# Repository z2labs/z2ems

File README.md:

# Z2 EMS

Electromagnetic simulation of printed circuit boards, straight from KiCad.

Z2 EMS is a distribution of [openEMS](https://openEMS.de) (the free FDTD field solver by Thorsten Liebig and
contributors) with the parts a PCB designer needs on top:

- **KiCad importer** (`CSXCAD.KiCadImport`): copper of every layer, plated holes, board outline and stackup are
  read straight from a `.kicad_pcb` file; two-pad R/L/C footprints become lumped elements. Fab stackup presets
  (`CSXCAD.FabStackups`, e.g. JLCPCB JLC04161H-7628) and laminate dispersion / copper roughness models
  (`CSXCAD.PCBMaterials`).
- **Board to S-parameters in one command** (`twin/kicad_sim.py`): lumped ports at the connector pads, an
  automatic mesh for PCB geometry (thirds rule on strip edges, diagonal tracks, via antipads, graded cells),
  one run per port, Touchstone output, Z0 and effective permittivity of a line, a mesh DRC that finds copper
  shorted or broken by the staircase mesh before a run.
- **CUDA engine** (`--engine=cuda`): the FDTD update, the absorbing boundaries, excitation, lumped RLC and
  dispersive materials on an NVIDIA GPU, with a memory guard that catches corrupted GPU memory instead of
  returning a wrong result.
- **Conformal PEC** (contour-path FDTD after Yu and Mittra, 2001): a Yee edge partly covered by metal
  keeps the free fraction of its length, so metal edges that do not fall on a mesh line are not snapped
  to it. On the 50 Ω test coupon this moves Z0 from 50.37 Ω (staircase) to 49.50 Ω, against 49.35 Ω
  from the closed-form formula. On by default in the twin, `Z2_CONFORMAL=0` turns it off.
- **Viewer and local server** (`gui/`): a browser 3D view of the board (exploded layers, components) that
  can also start runs and show S-parameters, field maps and far field.
- **KiCad plugin**: [z2labs/z2ems-kicad](https://github.com/z2labs/z2ems-kicad) drives all of the above from
  the PCB editor (ports, stackup, mesh preview, simulate, field overlays).

## Repository layout

```
openEMS/        submodule: z2labs/z2ems-openEMS  (openEMS + CUDA engine, conformal PEC)
CSXCAD/         submodule: z2labs/z2ems-CSXCAD   (CSXCAD + KiCad importer, fab stackups, PCB materials)
fparser, QCSXCAD, AppCSXCAD, CTB   submodules: upstream (thliebig)
twin/           KiCad board -> openEMS model -> S-parameters (see twin/README.md)
gui/            3D viewer and local simulation server (see gui/README.md)
examples/       test coupons and a worked antenna example (see examples/README.md)
scripts/        dependency installer, Python build, Windows bundling
doc-src/        openEMS documentation sources
```

## Install

**Windows:** download the engine package from the
[releases](https://github.com/z2labs/z2ems/releases) and unzip it, e.g. to `%LOCALAPPDATA%\Z2EMS\engine` (where
the KiCad plugin looks first). It contains the openEMS executables (CPU and CUDA engine), a Python with the
CSXCAD/openEMS bindings and all packages the twin needs, `twin/`, `gui/` and `examples/`. The CUDA engine needs
an NVIDIA driver; without one the CPU engine is used.

**Linux, from source:**

```bash
git clone --recursive https://github.com/z2labs/z2ems.git
cd z2ems
./scripts/install_deps.sh          # prints the package install command for your distribution
mkdir build && cd build
cmake .. -DCMAKE_INSTALL_PREFIX=$HOME/opt/z2ems -DBUILD_APPCSXCAD=NO \
         -DWITH_CUDA=ON -DCMAKE_CUDA_ARCHITECTURES="61;75;86;89"   # leave out both for a CPU-only build
make -j$(nproc)
cd .. && ./scripts/build_python.sh --cpp-install-dir $HOME/opt/z2ems   # CSXCAD + openEMS Python bindings
pip install numpy h5py matplotlib scipy shapely
export Z2_OPENEMS=$HOME/opt/z2ems/bin/openEMS
```

The CUDA engine needs a CUDA 12.x toolkit for Pascal GPUs (GTX 10xx, `61`); CUDA 13 dropped them.

## First run

```bash
cd twin
python kicad_sim.py ../examples/coupon_msl50.kicad_pcb --port J1 --port J2 --fmax 6e9            # CPU
python kicad_sim.py ../examples/coupon_msl50.kicad_pcb --port J1 --port J2 --fmax 6e9 --variant cuda
```

Expected: Z0 ≈ 49.5 Ω, εeff ≈ 3.35, |S11| about −28 dB or lower up to 6 GHz (−27.9 dB on the Windows CPU reference run). `twin/README.md` has the options, the
model rules, the environment switches and the validation cases.

## Relation to openEMS

The engine is openEMS with additions; models, scripts and post-processing written for openEMS run unchanged,
and the openEMS documentation at [docs.openEMS.de](https://docs.openems.de) applies.

## License

GPL-3.0, see [LICENSE](LICENSE); CSXCAD, QCSXCAD and fparser are LGPL-3.0, CTB is BSD-style. openEMS and CSXCAD
are © Thorsten Liebig and contributors; the Z2 EMS additions are © Zoltan Doczi / Z2Labs. Contributions follow [AI_POLICY.md](AI_POLICY.md) (disclosure and DCO sign-off).

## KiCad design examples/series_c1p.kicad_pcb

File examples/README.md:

# Examples

| file | what it is | run |
|---|---|---|
| `coupon_msl50.kicad_pcb` | 50 Ω microstrip, 40 mm, JLCPCB JLC04161H-7628 4-layer stackup, SMD launch pads J1/J2 | `python ../twin/kicad_sim.py coupon_msl50.kicad_pcb --port J1 --port J2 --fmax 6e9` → Z0 49.5 Ω, εeff 3.35 |
| `series_c1p.kicad_pcb` | the same line with a 1 pF series capacitor (C1) | add `--components` → \|S21\| −5.9 dB at 1 GHz (ideal 1 pF: −5.5 dB) |
| `dbg.kicad_pcb` | small 4-layer board used by the KiCad plugin's capability check | |
| `bwsma_air_launch_coupon.kicad_pcb` | 50 × 12 mm GCPW coupon with the "air" launch for the BAT Wireless BWSMA-KE-P001 edge SMA (LCSC C496550) | `python ../twin/make_panel.py out --sim 1` (connector model included) |
| `silabs-ams915/` | tools and results for the Silicon Labs MSC-AMS915 915 MHz antenna kit (NanoVNA measurement, PADS → KiCad import, Z2 EMS results) | see its README |

All boards open in KiCad 10. With the KiCad plugin installed, open a board and press the Z2Labs EMS buttons:
stackup preset, mesh preview, simulate, field overlay.

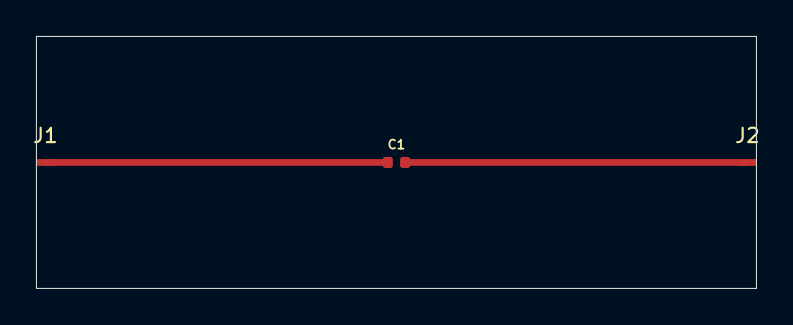
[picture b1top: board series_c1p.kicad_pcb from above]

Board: 4 copper layers, 40.0 x 14.0 mm, 3 parts (0 on the bottom side), 2 nets.

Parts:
C1: 1pF; C_0402_1005Metric
J1, J2: SMA edge launch; RF_Launch_Pad

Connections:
RF: C1.1, J1.1
RF2: C1.2, J2.1
